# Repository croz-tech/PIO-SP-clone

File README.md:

# PIO-SP-clone
A clone of the 1980s Cambridge Microelectronics (Camel Products) PIO-SP providing 8 latched inputs and 8 latched outputs for the ZX Spectrum range of machines on port 63 (decimal).

# From the original User Notes
This parallel input/output card allows the Sinclair Spectrum personal computer to control external hardware such as relays, indicators, transducers and motors.
Eight output channels and eight input channels are provided.  Both channels employ latches to obtain stable readings.  They may be used for eight bit bytes or to read or control single independent devices.  PIO-SP is located in the Spectrum's I/O map at address 63 (decimal). Both ports have the same address so BASIC or machine code IN and OUT commands can be used.  For example, OUT 63,85 will put an alternate pattern of ones and zeroes at the output port.  The input port has provision for strobing-in the exteral data.  If data is meant to be continuously read in the Spectrum, without attention from the outside then the ~STB pin should be connected to GND (fit JP1).  The Spectrum strobes the input latch when executing an IN command and therefore reads whatever is present in the 8 bit latch, while strobing in the new data at the same time.  All inputs and outputs are TTL compatibe and have high drive capabilities.
The unit plugs into the rear of the Spectrum. (note this unit does not currently include the male pass-through edge connector of the original)
Header connections are identical to the Camel Products PIO for ZX81. For convenience, in addition to the DIP-16 headers, a 20-way IDC header is also provided for more convenient connection/disconnection.

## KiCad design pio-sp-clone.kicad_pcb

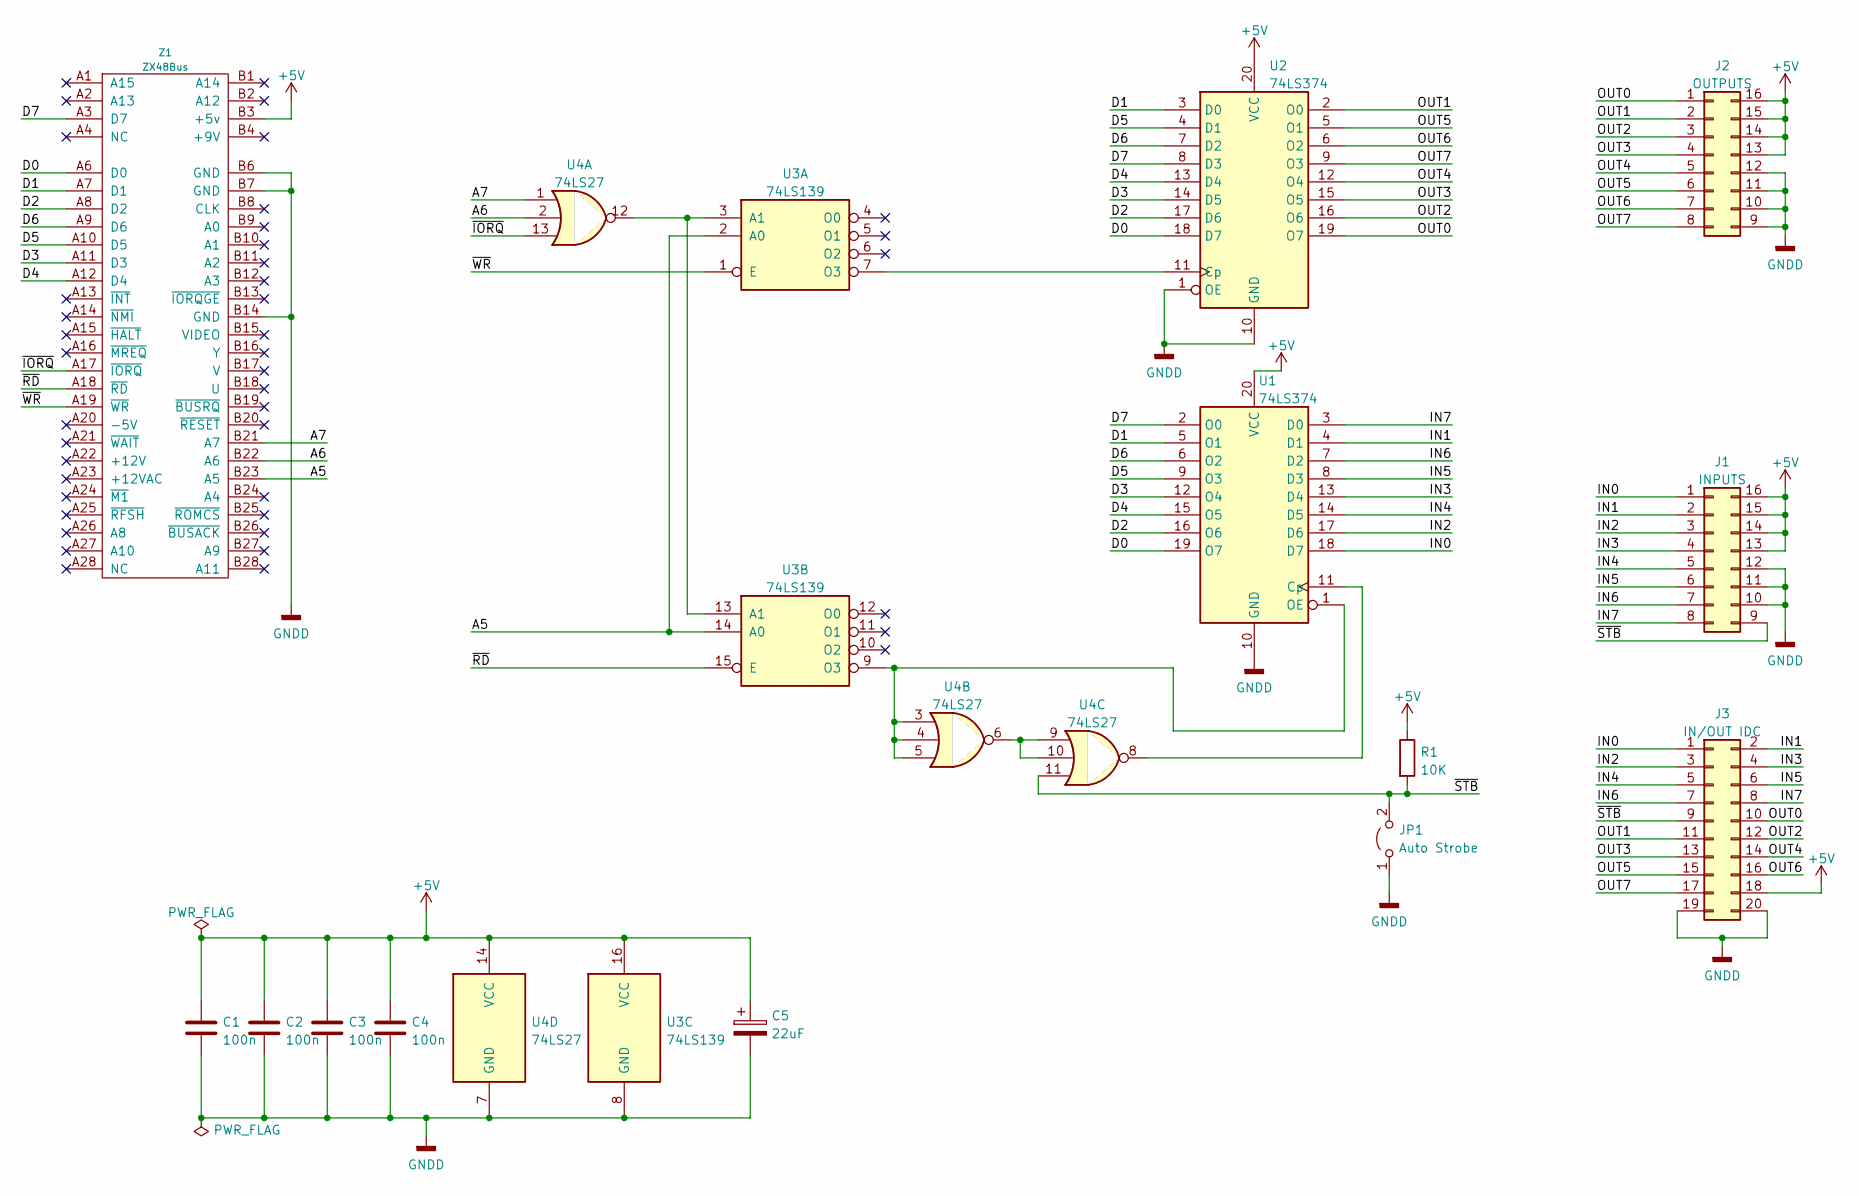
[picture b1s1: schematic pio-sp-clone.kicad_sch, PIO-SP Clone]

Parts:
C1, C2, C3, C4: 100n; C_Rect_L7.2mm_W2.5mm_P5.00mm_FKS2_FKP2_MKS2_MKP2
C5: 22uF; CP_Radial_D5.0mm_P2.00mm
J1: INPUTS; DIP-16_W7.62mm_Socket_LongPads
J2: OUTPUTS; DIP-16_W7.62mm_Socket_LongPads
J3: IN/OUT IDC; IDC-Header_2x10_P2.54mm_Latch_Horizontal
JP1: Auto Strobe; PinHeader_1x02_P2.54mm_Vertical
R1: 10K; R_Axial_DIN0207_L6.3mm_D2.5mm_P10.16mm_Horizontal
U1, U2: 74LS374; DIP-20_W7.62mm_Socket_LongPads
U3: 74LS139; DIP-16_W7.62mm_Socket_LongPads
U4: 74LS27; DIP-14_W7.62mm_Socket_LongPads
Z1: ZX48Bus; ZX_Bus_Pin_Header

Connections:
+5V: C1.1, C2.1, C3.1, C4.1, C5.1, J1.13, J1.14, J1.15, J1.16, J2.13, J2.14, J2.15, J2.16, J3.18, R1.1, U1.20 (VCC), U2.20 (VCC), U3.16 (VCC), U4.14 (VCC), Z1.B3 (+5v)
/A5: U3.2 (A0), U3.14 (A0), Z1.B23 (A5)
/A6: U4.2, Z1.B22 (A6)
/A7: U4.1, Z1.B21 (A7)
/D0: U1.19 (O7), U2.18 (D7), Z1.A6 (D0)
/D1: U1.5 (O1), U2.3 (D0), Z1.A7 (D1)
/D2: U1.16 (O6), U2.17 (D6), Z1.A8 (D2)
/D3: U1.12 (O4), U2.14 (D5), Z1.A11 (D3)
/D4: U1.15 (O5), U2.13 (D4), Z1.A12 (D4)
/D5: U1.9 (O3), U2.4 (D1), Z1.A10 (D5)
/D6: U1.6 (O2), U2.7 (D2), Z1.A9 (D6)
/D7: U1.2 (O0), U2.8 (D3), Z1.A3 (D7)
/IN0: J1.1, J3.1, U1.18 (D7)
/IN1: J1.2, J3.2, U1.4 (D1)
/IN2: J1.3, J3.3, U1.17 (D6)
/IN3: J1.4, J3.4, U1.13 (D4)
/IN4: J1.5, J3.5, U1.14 (D5)
/IN5: J1.6, J3.6, U1.8 (D3)
/IN6: J1.7, J3.7, U1.7 (D2)
/IN7: J1.8, J3.8, U1.3 (D0)
/OUT0: J2.1, J3.10, U2.19 (O7)
/OUT1: J2.2, J3.11, U2.2 (O0)
/OUT2: J2.3, J3.12, U2.16 (O6)
/OUT3: J2.4, J3.13, U2.15 (O5)
/OUT4: J2.5, J3.14, U2.12 (O4)
/OUT5: J2.6, J3.15, U2.5 (O1)
/OUT6: J2.7, J3.16, U2.6 (O2)
/OUT7: J2.8, J3.17, U2.9 (O3)
/~IORQ: U4.13, Z1.A17 (~IORQ)
/~RD: U3.15 (E), Z1.A18 (~RD)
/~STB: J1.9, J3.9, JP1.2 (B), R1.2, U4.11
/~WR: U3.1 (E), Z1.A19 (~WR)
GNDD: C1.2, C2.2, C3.2, C4.2, C5.2, J1.10, J1.11, J1.12, J2.9, J2.10, J2.11, J2.12, J3.19, J3.20, JP1.1 (A), U1.10 (GND), U2.1 (OE), U2.10 (GND), U3.8 (GND), U4.7 (GND), Z1.B6 (GND), Z1.B7 (GND), Z1.B14 (GND)
unnamed: U1.1 (OE), U3.9 (O3), U4.3, U4.4, U4.5
unnamed: U1.11 (Cp), U4.8
unnamed: U2.11 (Cp), U3.7 (O3)
unnamed: U3.3 (A1), U3.13 (A1), U4.12
unnamed: U4.6, U4.9, U4.10

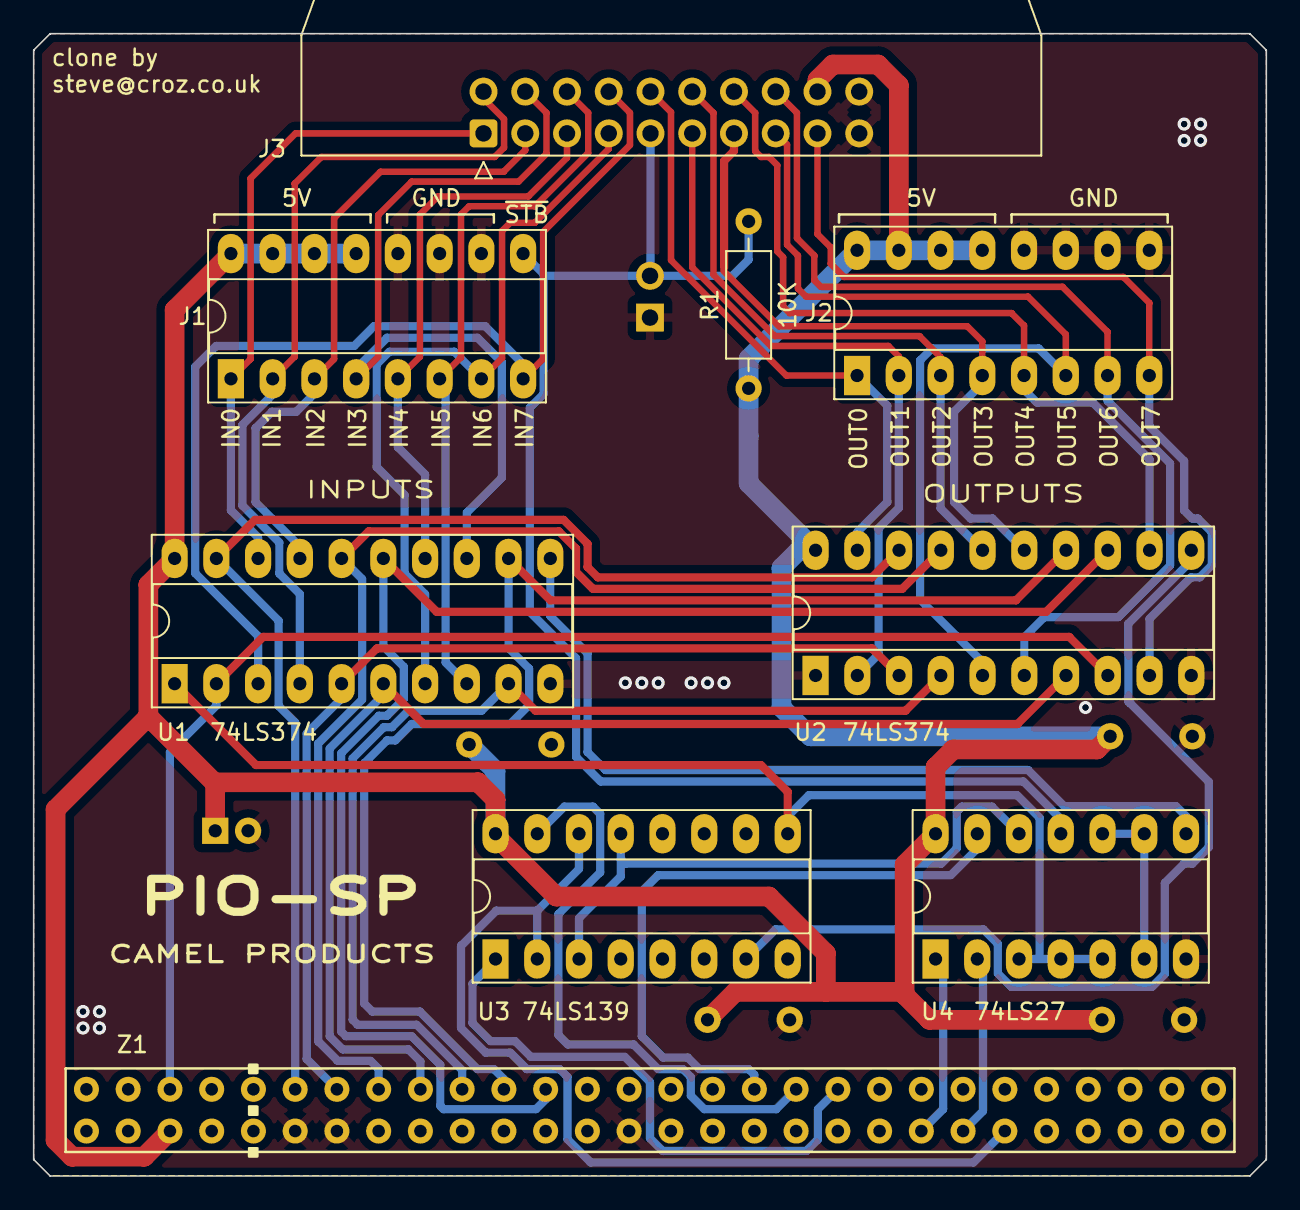
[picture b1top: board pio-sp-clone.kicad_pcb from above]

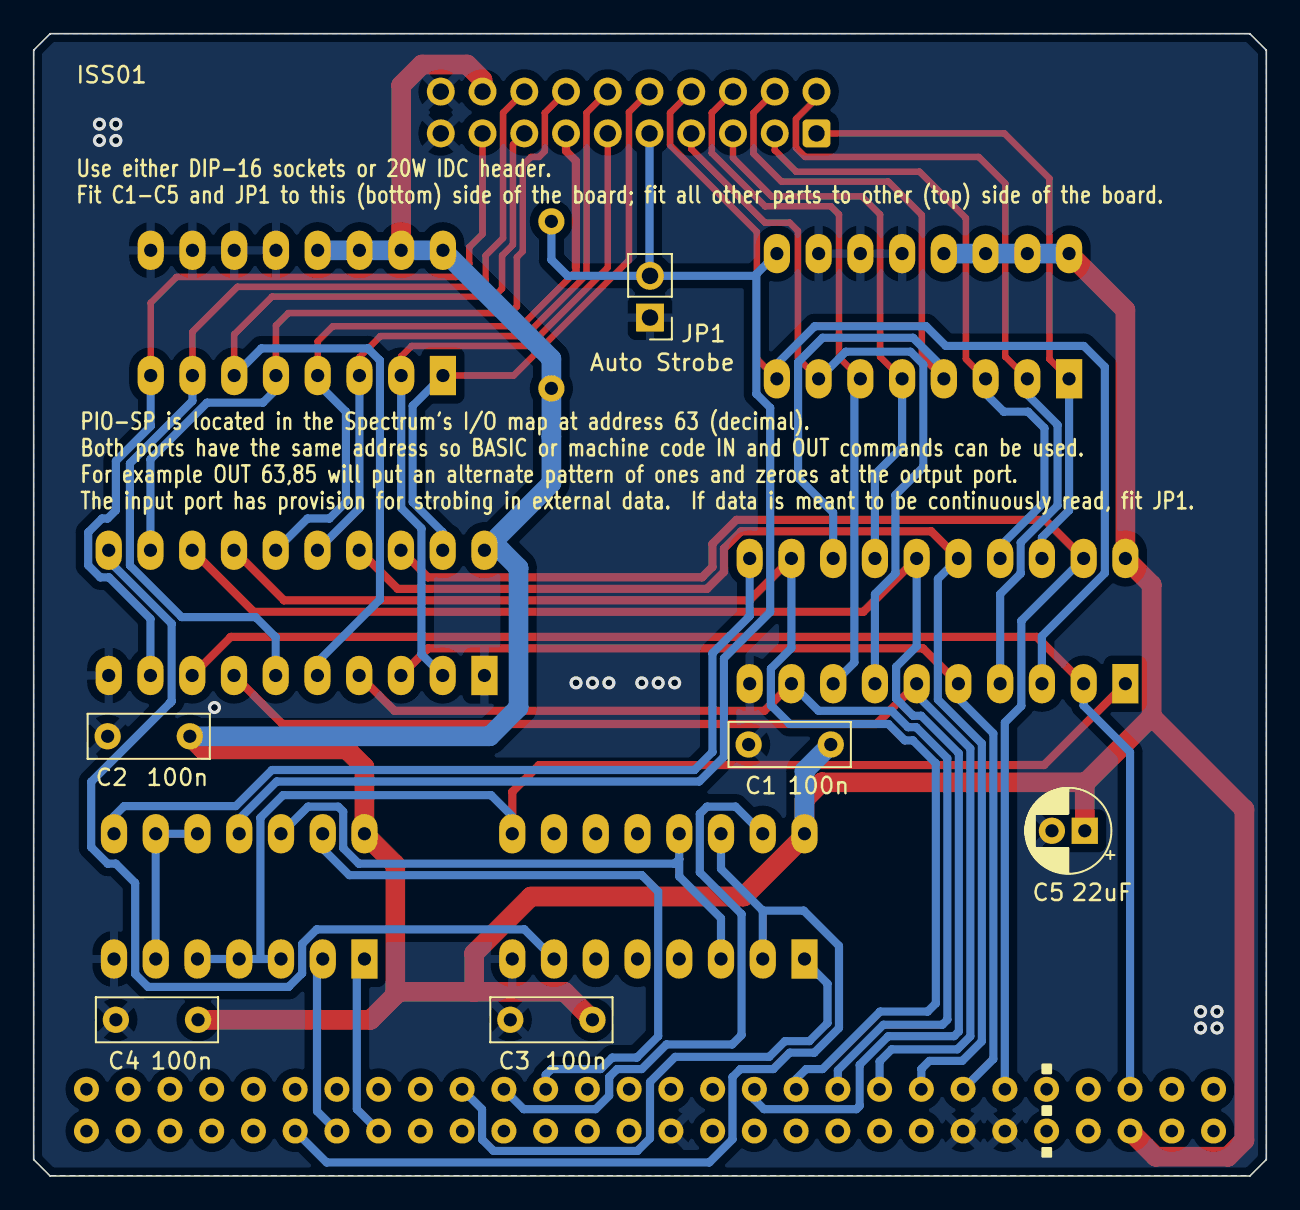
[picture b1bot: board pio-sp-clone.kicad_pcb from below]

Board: 2 copper layers, 75.0 x 69.5 mm, 15 parts (6 on the bottom side), 38 nets.

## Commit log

2023-11-24 added original documentation
